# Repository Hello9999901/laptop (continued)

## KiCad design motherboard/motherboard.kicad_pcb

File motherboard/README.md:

# Motherboard

Too much to explain right now.

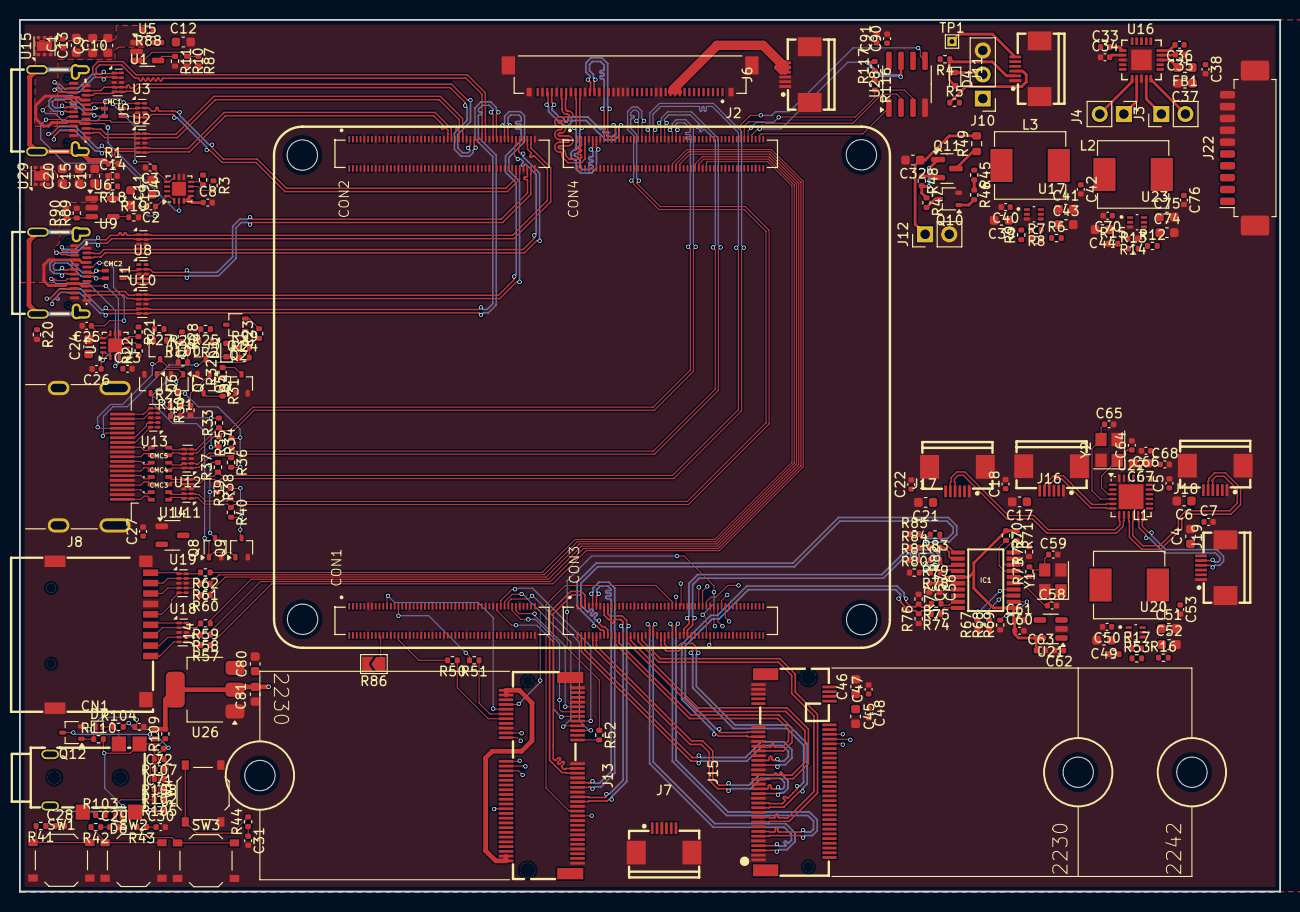
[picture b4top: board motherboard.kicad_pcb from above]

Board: 6 copper layers, 133.0 x 92.0 mm, 257 parts (0 on the bottom side), 253 nets.

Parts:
C1, C14: 100nF (+25V); C_0402_1005Metric
C2, C3, C25, C26: 220pF; C_0402_1005Metric
C4, C6, C11, C12, C13, C17, C19, C20, C21, C24, C32, C37, C67, C80, C81: 10uF; C_0603_1608Metric
C5, C7, C18, C22, C38, C48, C66, C71, C72, C90: 0.1uF; C_0402_1005Metric
C8, C23, C40, C42, C50, C53, C56, C61, C70, C76: 100nF; C_0402_1005Metric
C9, C10, C15, C16: 10uF (C913517); C_0603_1608Metric
C27, C33, C34, C35, C36, C47, C57, C60, C62, C63, C68, C73, C91: 1uF; C_0402_1005Metric
C28, C29, C30, C31: 1nF; C_0402_1005Metric
C39, C41, C43, C44, C45, C46, C49, C51, C52, C74, C75: 22uF; C_0603_1608Metric
C58, C59, C64, C65: 15pF; C_0402_1005Metric
CMC1, CMC2, CMC3, CMC4, CMC5, CMC6: ACM2012; FIL_ACM2012-900-2P-T001
CN1: PJ-332A-6A (3.5mm Jack); AUDIO-SMD_PJ-332A-6A
D3, D4: LRB521S-30T1G; D_SOD-523
D6, D7: LESD8D5.0CB1T5G; D_SOD-882
FB1: GZ1608D601TF; L_0603_1608Metric
IC1: PI6C557-05BLE; SOP65P640X120-20N
J1: USB_C_Receptacle; USB-C-SMD_TYPE-C-24P-QT
J2: 20455-040E-76 OLED IPEX; IPEX_20455-040E-76
J3: RIGHT SPEAKERS; PinHeader_1x02_P2.54mm_Vertical
J4: LEFT SPEAKERS; PinHeader_1x02_P2.54mm_Vertical
J5: Outer USB-C; USB-C-SMD_TYPE-C-24P-QT
J6: OLED EL POWER; FPC-SMD_6P-P0.50_XUNPU_FPC-05F-6PH20
J7: HALL SWITCH; FPC-SMD_6P-P0.50_XUNPU_FPC-05F-6PH20
J8: HDMI_A; HDMI_A_Molex_208658-1001_Horizontal
J10: DEBUG UART; PinHeader_1x03_P2.54mm_Vertical
J11: SYSTEM; FPC-SMD_6P-P0.50_XUNPU_FPC-05F-6PH20
J12: 5V FAN; PinHeader_1x02_P2.54mm_Vertical
J13: Bus_M.2_Socket_E; CONN-SMD_APCI0147-P001A
J14: Micro_SD_Card_Det1; TF-SMD_TF-CARD-H1.8
J15: Bus_M.2_Socket_M; CONN-SMD_AS0BC21-S30BM-7H
J16, J17, J18, J19: USB; FPC-SMD_6P-P0.50_XUNPU_FPC-05F-6PH20
J20: CM3588 Hirose Connector; CM3588
J22: BATTERY IN; Molex_PicoBlade_53261-1071_1x10-1MP_P1.25mm_Horizontal
L1, L3: MWSA0603S-3R3MT; L_Sunlord_MWSA0603S
L2: FXL0630-4R7-M; L_Sunlord_MWSA0603S
Q1, Q2, Q4, Q5, Q10, Q12: 2SK3018W; SOT-323_SC-70
Q3: L2N7002WT1G; SOT-323_SC-70
Q6, Q7, Q8, Q9: WNM6002-3/TR; SOT-323_SC-70
Q11: AO3415A; SOT-23
R1, R20: 1M; R_0402_1005Metric
R2, R3, R21, R22, R52, R111: 2.2k; R_0402_1005Metric
R4, R6, R7, R12, R16, R25, R27, R31, R32, R45, R54, R70, R71, R105, R106, R110, R116, R117: 10k; R_0402_1005Metric
R5, R57, R58, R59, R60, R61, R62, R74, R75, R78, R79, R82, R83, R107, R108: 33R; R_0402_1005Metric
R8, R17: 49.9k; R_0402_1005Metric
R9, R53: 510k; R_0402_1005Metric
R10, R87, R89, R90: 6.8k; R_0402_1005Metric
R11, R19, R109: 100k; R_0402_1005Metric
R13: 220k; R_0402_1005Metric
R14: 33k; R_0402_1005Metric
R15: 330k; R_0402_1005Metric
R18, R50, R51, R68, R69, R88, R102, R103, R104: 0R; R_0402_1005Metric
R23: 27k; R_0402_1005Metric
R24, R100, R101: 18k; R_0402_1005Metric
R26, R29, R99: 2k; R_0402_1005Metric
R28, R47: 1k; R_0402_1005Metric
R30: 47k; R_0402_1005Metric
R33, R34, R35, R36, R37, R38, R39, R40: 499R; R_0402_1005Metric
R41, R42, R43, R44, R46, R73: 100R; R_0402_1005Metric
R48, R72: 470R; R_0402_1005Metric
R49: 2.2R; R_0603_1608Metric
R67: 4.7k; R_0402_1005Metric
R76, R77, R80, R81, R84, R85: 49.9R; R_0402_1005Metric
R86: 0R; SolderJumper-2_P1.3mm_Open_TrianglePad1.0x1.5mm
SW1: PWR; SW_Push_1P1T_XKB_TS-1187A
SW2: RESET; SW_Push_1P1T_XKB_TS-1187A
SW3: MASK; SW_Push_1P1T_XKB_TS-1187A
SW4: RECOVERY; SW_Push_1P1T_XKB_TS-1187A
TP1: PWRON; TestPoint_THTPad_1.0x1.0mm_Drill0.5mm
U1, U2, U3, U8, U9, U10, U11, U12, U13, U18, U19: TPD4E02B04; USON-10_2.5x1.0mm_P0.5mm
U4, U7: FUSB302BMPX; WQFN-14-1EP_2.5x2.5mm_P0.5mm_EP1.45x1.45mm
U5, U6: SY6280AAC; SOT-23-5
U14: AP2331; SOT-23-3
U15, U29: TVS2200DRV; WSON-6-1EP_2x2mm_P0.65mm_EP1x1.6mm
U16: TPA2016D2RTJR; QFN50P400X400X80-21N
U17, U20, U23: TPS564257DRLR; SOT50P160X60-6N
U21: AP2127K-3.3; SOT-23-5
U22: CH334F; QFN-24-1EP_4x4mm_P0.5mm_EP2.6x2.6mm
U26: AMS1117-1.8; SOT-223-3_TabPin2
U28: SPI Flash; SOIC-8_3.9x4.9mm_P1.27mm
Y1: 25MHz; Crystal_SMD_3225-4Pin_3.2x2.5mm
Y2: 12MHz; Crystal_SMD_3225-4Pin_3.2x2.5mm

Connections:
+1V8: C81.1, R45.1, R109.2, R111.2, U26.2 (VO)
+3.3V: C8.1, C23.1, C41.1, C42.1, C43.1, C66.1, C67.1, C80.1, C90.1, C91.1, J2.17, J2.18, J2.19, J7.1, L3.2, Q2.1 (G), R2.1, R3.1, R4.2, R6.2, R21.1, R22.1, R23.1, R25.1, R27.1, R28.1, R31.1, R32.1, R116.1, R117.1, U4.3 (VDD), U4.4 (VDD), U7.3 (VDD), U7.4 (VDD), U21.3 (EN), U22.20 (VDD33), U26.3 (VI), U28.8 (VCC)
+3.3V_PCIE: C45.1, C46.1, C47.1, C48.1, C51.1, C52.1, C53.1, J13.2 (3.3V), J13.4 (3.3V), J13.72 (3.3V), J13.74 (3.3V), J15.2 (3.3V), J15.4 (3.3V), J15.12 (3.3V), J15.14 (3.3V), J15.16 (3.3V), J15.18 (3.3V), J15.70 (3.3V), J15.72 (3.3V), J15.74 (3.3V), L1.2, R16.2
+5V: C4.1, C5.1, C6.1, C7.1, C11.1, C12.1, C17.1, C18.1, C19.1, C21.1, C22.1, C24.1, C37.1, C38.1, C62.1, C68.1, C74.1, C75.1, C76.1, D3.2 (A), FB1.1, J16.6, J17.6, J18.6, J19.6, L2.2, Q1.1 (G), Q11.2 (S), R12.2, R18.1, R48.1, R88.1, U4.12 (VCONN), U4.13 (VCONN), U5.5 (IN), U6.5 (IN), U7.12 (VCONN), U7.13 (VCONN), U14.3 (IN), U16.4 (PVDDL_2), U16.5 (PVDDL), U16.11 (PVDDR_2), U16.12 (PVDDR), U21.1 (VIN), U22.19 (V5)
/Audio/L_AUDIO: C33.1, C72.1, J20.104, R104.2, R106.2
/Audio/L_DET: CN1.5, CN1.6, R109.1, R110.2
/Audio/L_HP: CN1.4, D7.2 (A2), R104.1
/Audio/MIC: CN1.1, R102.1
/Audio/R_AUDIO: C36.1, C71.1, J20.103, R103.2, R105.2
/Audio/R_HP: CN1.3, D6.2 (A2), R103.1
/BOOT_SARADC_IN0: C30.1, J20.15, R43.1
/GPIO0_A4/SDMMC_DET_L: J20.370, R62.1
/GPIO0_B2: J13.21 (~SDIO_WAKE), J20.247
/GPIO0_C4/UART0_RX_M0: J20.270, R52.1
/GPIO0_C5/UART0_TX_M0/PWM4_M0: J13.20 (~UART_WAKE), J20.272
/GPIO0_D3/CC_INT_L: J20.264, U4.5 (INT_N)
/GPIO0_D5: J20.268, U7.5 (INT_N)
/GPIO1_A0/UART6_RX_M1: J13.22 (UART_RXD), J20.273
/GPIO1_A1/UART6_TX_M1: J13.32 (UART_TXD), J20.275
/GPIO1_A2/I2C4_SDA_M3_TP: J13.36 (UART_RTS), J20.277
/GPIO1_A3/I2C4_SCL_M3_TP: J13.34 (UART_CTS), J20.279
/GPIO1_A4: J20.281, U28.6 (SCK)
/GPIO1_A7: J20.283, U16.18 (SDZ)
/GPIO1_C4/HP_DET_L: J20.108, Q12.3 (D), R111.1
/GPIO1_D2/TYPEC5V_PWREN_H: J20.239, R11.1, R19.1, U5.4 (ON), U6.4 (ON)
/GPIO1_D3/PWM1_M1: J20.241, R45.2, R46.1
/GPIO2_A6: J13.13 (SDIO_DATA0), J20.79
/GPIO2_A7: J13.15 (SDIO_DATA1), J20.81
/GPIO2_B0: J13.17 (SDIO_DATA2), J20.83
/GPIO2_B1: J13.19 (SDIO_DATA3), J20.85
/GPIO2_B2: J13.11 (SDIO_CMD), J20.87
/GPIO2_B3: J13.9 (SDIO_CLK), J20.89
/GPIO2_B7: J13.8 (PCM_CLK/I2S_SCK), J20.99
/GPIO2_C0: J13.10 (PCM_SYNC/I2S_WS), J20.21
/GPIO2_C3: J20.27, R51.2
/GPIO3_A0/SPI4_MISO_M1/PWM10_M0: J20.387, U28.5 (SI/IO0)
/GPIO3_A1/SPI4_MOSI_M1: J20.389, U28.2 (SO/IO1)
/GPIO3_A2/SPI4_CLK_M1/UART8_TX_M1: J20.391, R116.2, U28.3 (~WP/IO2)
/GPIO3_A3/SPI4_CS0_M1/UART8_RX_M1: J20.393, R117.2, U28.7 (~HOLD/IO3)
/GPIO3_A5: J20.397, U28.1 (~CS)
/GPIO3_A6/LCD_RST: J13.42 (VENDOR_DEFINED), J20.399
/GPIO4_A0/TP_2_INT_L: J13.53 (~CLKREQ0), J20.251
/GPIO4_A1/TP_2_RST_L: J13.55 (~PEWAKE0), J20.253
/GPIO4_A2: J13.52 (~PERST0), J20.255
/GPIO4_B4/PCIE30X4_CLKREQn_M1_L: J15.52 (~CLKREQ), J20.265
/GPIO4_B5/PCIE30X4_WAKEn_M1_L: J15.54 (~PEWAKE), J20.267
/GPIO4_B6/PCIE30X4_PERSTn_M1_L: J15.50 (~PERST), J20.269
/GPIO4_C2: J7.2, J20.26
/GPIO4_C3: J20.28, R50.2
/HDMI0_TX_ON_H: J20.369, Q6.1 (G), Q7.1 (G), Q8.1 (G), Q9.1 (G)
/HDMI1_TX0N: J2.29, J20.317
/HDMI1_TX0P: J2.28, J20.315
/HDMI1_TX1N: J2.32, J20.311
/HDMI1_TX1P: J2.31, J20.309
/HDMI1_TX2N: J2.35, J20.305
/HDMI1_TX2P: J2.34, J20.303
/HDMI1_TX3N: J2.38, J20.323
/HDMI1_TX3P: J2.37, J20.321
/HDMI1_TX_SBDN: J2.25, J20.329
/HDMI1_TX_SBDP: J2.26, J20.327
/HDMITX0_CEC_M0: J20.367, Q1.2 (S), R23.2
/HDMITX0_HPDIN_M0: J20.295, Q5.3 (D), R32.2
/HDMITX0_SCL_M0: J20.363, Q2.2 (S), R25.2
/HDMITX0_SDA_M0: J20.365, Q3.2 (S), R27.2
/HDMI_TX/CEC: J8.13 (CEC), Q1.3 (D), U13.1 (D1+), U13.10 (NC)
/HDMI_TX/HDMI0_5V: C27.1, J8.18 (+5V), U13.4 (D2+), U13.7 (NC), U14.2 (OUT)
/HDMI_TX/HDMI0_TX0N: CMC5.4, J20.347, R35.1, U12.2 (D1-), U12.9 (NC)
/HDMI_TX/HDMI0_TX0P: CMC5.3, J20.345, R36.1, U12.1 (D1+), U12.10 (NC)
/HDMI_TX/HDMI0_TX1N: CMC4.4, J20.341, R37.1, U11.5 (D2-), U11.6 (NC)
/HDMI_TX/HDMI0_TX1P: CMC4.3, J20.339, R38.1, U11.4 (D2+), U11.7 (NC)
/HDMI_TX/HDMI0_TX2N: CMC3.4, J20.335, R39.1, U11.2 (D1-), U11.9 (NC)
/HDMI_TX/HDMI0_TX2P: CMC3.3, J20.333, R40.1, U11.1 (D1+), U11.10 (NC)
/HDMI_TX/HDMI0_TX3N: CMC6.4, J20.353, R33.1, U12.5 (D2-), U12.6 (NC)
/HDMI_TX/HDMI0_TX3P: CMC6.3, J20.351, R34.1, U12.4 (D2+), U12.7 (NC)
/HDMI_TX/IN_TX0N: CMC5.1, J8.9 (D0-)
/HDMI_TX/IN_TX0P: CMC5.2, J8.7 (D0+)
/HDMI_TX/IN_TX1N: CMC4.1, J8.6 (D1-)
/HDMI_TX/IN_TX1P: CMC4.2, J8.4 (D1+)
/HDMI_TX/IN_TX2N: CMC3.1, J8.3 (D2-)
/HDMI_TX/IN_TX2P: CMC3.2, J8.1 (D2+)
/HDMI_TX/IN_TX3N: CMC6.1, J8.12 (CK-)
/HDMI_TX/IN_TX3P: CMC6.2, J8.10 (CK+)
/HDMI_TX/SBDN: J8.19 (HPD), J20.359, R29.1, R101.1, U13.5 (D2-), U13.6 (NC)
/HDMI_TX/SBDP: J8.14 (UTILITY), J20.357, U13.2 (D1-), U13.9 (NC)
/HDMI_TX/SCL: J8.15 (SCL), Q2.3 (D), R24.2, R99.2
/HDMI_TX/SDA: J8.16 (SDA), Q3.3 (D), R26.2, R100.2
/I2C6_SCL_M0: J20.296, R3.2, U4.6 (SCL), U16.19 (SDA)
/I2C6_SDA_M0: J20.298, R2.2, U4.7 (SDA), U16.17 (SCL)
/I2C7_SCL_M0: J20.107, R22.2, U7.6 (SCL)
/I2C7_SDA_M0: J20.105, R21.2, U7.7 (SDA)
/MIC_IN: J20.106, R102.2
/PCIE3.0-MKEY/+3.3V_PI6C: C56.1, C57.1, C60.1, C61.1, C63.1, IC1.1 (VDDXD), IC1.15 (VDDODA), R70.1, R71.1, U21.5 (VOUT)
/PCIE3.0-MKEY/CLK2N: IC1.13 (~CLK2), R79.1
/PCIE3.0-MKEY/CLK2P: IC1.14 (CLK2), R78.1
/PCIE3.0-MKEY/CLK3N: IC1.11 (~CLK3), R83.1
/PCIE3.0-MKEY/CLK3P: IC1.12 (CLK3), R82.1
/PCIE3.0-MKEY/PCIE30_REFCLK_A_N: J15.53 (REFCLKn), R75.2, R77.2
/PCIE3.0-MKEY/PCIE30_REFCLK_A_P: J15.55 (REFCLKp), R74.2, R76.2
/PCIE3.0-MKEY/X1: C58.1, IC1.5 (X1), Y1.1
/PCIE3.0-MKEY/X2: IC1.6 (X2), R73.1
/PCIE20_1_REFCLKN: J13.49 (REFCLKn0), J20.217
/PCIE20_1_REFCLKP: J13.47 (REFCLKp0), J20.215
/PCIE20_1_RXN: J13.41 (PERp0), J20.211
/PCIE20_1_RXP: J13.43 (PERn0), J20.209
/PCIE20_1_TXN: J13.37 (PETn0), J20.205
/PCIE20_1_TXP: J13.35 (PETp0), J20.203
/PCIE30_PORT0_REFCLKN: J20.218, R83.2, R85.2
/PCIE30_PORT0_REFCLKP: J20.216, R82.2, R84.2
/PCIE30_PORT0_RX0N: J15.41 (PERn0/SATA-B+), J20.206
/PCIE30_PORT0_RX0P: J15.43 (PERp0/SATA-B-), J20.204
/PCIE30_PORT0_RX1N: J15.29 (PERn1), J20.212
/PCIE30_PORT0_RX1P: J15.31 (PERp1), J20.210
/PCIE30_PORT0_TX0N: J15.47 (PETn0/SATA-A-), J20.224
/PCIE30_PORT0_TX0P: J15.49 (PETp0/SATA-A+), J20.222
/PCIE30_PORT0_TX1N: J15.35 (PETn1), J20.230
/PCIE30_PORT0_TX1P: J15.37 (PETp1), J20.228
/PCIE30_PORT1_REFCLKN: J20.260, R79.2, R81.2
/PCIE30_PORT1_REFCLKP: J20.258, R78.2, R80.2
/PCIE30_PORT1_RX2N: J15.17 (PERn2), J20.236
/PCIE30_PORT1_RX2P: J15.19 (PERp2), J20.234
/PCIE30_PORT1_RX3N: J15.5 (PERn3), J20.242
/PCIE30_PORT1_RX3P: J15.7 (PERp3), J20.240
/PCIE30_PORT1_TX2N: J15.23 (PETn2), J20.248
/PCIE30_PORT1_TX2P: J15.25 (PETp2), J20.246
/PCIE30_PORT1_TX3N: J15.11 (PETn3), J20.254
/PCIE30_PORT1_TX3P: J15.13 (PETp3), J20.252
/PMIC_EXT_EN_OUT: J20.19, U17.5 (EN), U20.5 (EN), U23.5 (EN)
/PWRON_L: C28.1, J20.17, R41.1
/RECOVERY: C31.1, J20.101, R44.1
/RESET_L: C29.1, J20.16, R42.1
/SD Card/CLK: J14.5 (CLK), J20.360, U19.5 (D2-), U19.6 (NC)
/SD Card/CMD: J14.3 (CMD), R59.2, U18.2 (D1-), U18.9 (NC)
/SD Card/D0: J14.7 (DAT0), R60.2, U19.4 (D2+), U19.7 (NC)
/SD Card/D1: J14.8 (DAT1), R61.2, U19.2 (D1-), U19.9 (NC)
/SD Card/D2: J14.1 (DAT2), R57.2, U18.5 (D2-), U18.6 (NC)
/SD Card/D3: J14.2 (DAT3/CD), R58.2, U18.4 (D2+), U18.7 (NC)
/SD Card/DET: J14.9 (DET), R62.2, U19.1 (D1+), U19.10 (NC)
/SD Card/VDD: J14.4 (VDD), J20.358, U18.1 (D1+), U18.10 (NC)
/SDMMC0_CMD: J20.356, R59.1
/SDMMC0_D0: J20.364, R60.1
/SDMMC0_D1: J20.366, R61.1
/SDMMC0_D2: J20.352, R57.1
/SDMMC0_D3: J20.354, R58.1
/System/BOOT_SARADC: J11.4, R43.2, SW3.1 (A)
/System/PWRON_L_IN: J11.6, R41.2, SW1.1 (A), TP1.1
/System/RECOVERY_IN: R44.2, SW4.1 (A)
/System/RESET_L_IN: J11.5, R42.2, SW2.1 (A)
/System/UART_RX: D4.2 (A), J11.2, J20.22, R4.1
/System/UART_TX: J11.3, J20.20, R5.1
/USB2.0/D1_N: J19.5, U22.11 (DM1)
/USB2.0/D1_P: J19.4, U22.12 (DP1)
/USB2.0/D2_N: J18.5, U22.9 (DM2)
/USB2.0/D2_P: J18.4, U22.10 (DP2)
/USB2.0/D3_N: J17.5, U22.7 (DM3)
/USB2.0/D3_P: J17.4, U22.8 (DP3)
/USB2.0/D4_N: J16.5, U22.5 (DM4)
/USB2.0/D4_P: J16.4, U22.6 (DP4)
/USB2.0/X1: C64.1, U22.3 (XO), Y2.1
/USB2.0/X2: C65.1, U22.4 (XI), Y2.3
/USB20_HOST0_DN: J20.324, U22.14 (DMU)
/USB20_HOST0_DP: J20.322, U22.15 (DPU)
/USB20_HOST1_DN: J13.5 (USB_D-), J20.318
/USB20_HOST1_DP: J13.3 (USB_D+), J20.316
/USBC0/CC1: C3.1, J5.A5 (CC1), U4.10 (CC1), U4.11 (CC1)
/USBC0/CC2: C2.1, J5.B5 (CC2), U4.1 (CC2), U4.14 (CC2)
/USBC0/D+: CMC1.4, J20.190, U3.2 (D1-), U3.9 (NC)
/USBC0/D-: CMC1.3, J20.192, U3.4 (D2+), U3.7 (NC)
/USBC0/IN_D+: CMC1.1, J5.A6 (D+), J5.B6 (D+)
/USBC0/IN_D-: CMC1.2, J5.A7 (D-), J5.B7 (D-)
/USBC0/RX1+: J5.B11 (RX1+), J20.171, U1.1 (D1+), U1.10 (NC)
/USBC0/RX1-: J5.B10 (RX1-), J20.173, U1.2 (D1-), U1.9 (NC)
/USBC0/RX2+: J5.A11 (RX2+), J20.159, U2.2 (D1-), U2.9 (NC)
/USBC0/RX2-: J5.A10 (RX2-), J20.161, U2.1 (D1+), U2.10 (NC)
/USBC0/SBUS1: J5.A8 (SBU1), J20.304, U3.5 (D2-), U3.6 (NC)
/USBC0/SBUS2: J5.B8 (SBU2), J20.306, U3.1 (D1+), U3.10 (NC)
/USBC0/TX1+: J5.A2 (TX1+), J20.165, U1.4 (D2+), U1.7 (NC)
/USBC0/TX1-: J5.A3 (TX1-), J20.167, U1.5 (D2-), U1.6 (NC)
/USBC0/TX2+: J5.B2 (TX2+), J20.153, U2.5 (D2-), U2.6 (NC)
/USBC0/TX2-: J5.B3 (TX2-), J20.155, U2.4 (D2+), U2.7 (NC)
/USBC0/VBUS: C1.1, C9.1, C10.1, C13.1, J5.A4 (VBUS), J5.A9 (VBUS), J5.B4 (VBUS), J5.B9 (VBUS), R88.2, U4.2 (VBUS), U5.1 (OUT), U15.1 (GND), U15.2 (GND), U15.3 (GND), U15.7 (GND)
/USBC1/CC1: C25.1, J1.A5 (CC1), U7.10 (CC1), U7.11 (CC1)
/USBC1/CC2: C26.1, J1.B5 (CC2), U7.1 (CC2), U7.14 (CC2)
/USBC1/D+: CMC2.4, J20.196, U8.2 (D1-), U8.9 (NC)
/USBC1/D-: CMC2.3, J20.198, U8.4 (D2+), U8.7 (NC)
/USBC1/IN_D+: CMC2.1, J1.A6 (D+), J1.B6 (D+)
/USBC1/IN_D-: CMC2.2, J1.A7 (D-), J1.B7 (D-)
/USBC1/RX1+: J1.B11 (RX1+), J20.195, U9.1 (D1+), U9.10 (NC)
/USBC1/RX1-: J1.B10 (RX1-), J20.197, U9.2 (D1-), U9.9 (NC)
/USBC1/RX2+: J1.A11 (RX2+), J20.183, U10.2 (D1-), U10.9 (NC)
/USBC1/RX2-: J1.A10 (RX2-), J20.185, U10.1 (D1+), U10.10 (NC)
/USBC1/SBUS1: J1.A8 (SBU1), J20.310, U8.5 (D2-), U8.6 (NC)
/USBC1/SBUS2: J1.B8 (SBU2), J20.312, U8.1 (D1+), U8.10 (NC)
/USBC1/TX1+: J1.A2 (TX1+), J20.189, U9.4 (D2+), U9.7 (NC)
/USBC1/TX1-: J1.A3 (TX1-), J20.191, U9.5 (D2-), U9.6 (NC)
/USBC1/TX2+: J1.B2 (TX2+), J20.177, U10.5 (D2-), U10.6 (NC)
/USBC1/TX2-: J1.B3 (TX2-), J20.179, U10.4 (D2+), U10.7 (NC)
/USBC1/VBUS: C14.1, C15.1, C16.1, C20.1, J1.A4 (VBUS), J1.A9 (VBUS), J1.B4 (VBUS), J1.B9 (VBUS), R18.2, U6.1 (OUT), U7.2 (VBUS), U29.1 (GND), U29.2 (GND), U29.3 (GND), U29.7 (GND)
/VDC_MODE: J20.18, R86.1
GND: C1.2, C2.2, C3.2, C4.2, C5.2, C6.2, C7.2, C8.2, C9.2, C10.2, C11.2, C12.2, C13.2, C14.2, C15.2, C16.2, C17.2, C18.2, C19.2, C20.2, C21.2, C22.2, C23.2, C24.2, C25.2, C26.2, C27.2, C28.2, C29.2, C30.2, C31.2, C32.2, C34.1, C35.1, C37.2, C38.2, C39.2, C40.2, C41.2, C42.2, C43.2, C44.2, C45.2, C46.2, C47.2, C48.2, C49.2, C50.2, C51.2, C52.2, C53.2, C56.2, C57.2, C58.2, C59.2, C60.2, C61.2, C62.2, C63.2, C64.2, C65.2, C66.2, C67.2, C68.2, C70.2, C73.2, C74.2, C75.2, C76.2, C80.2, C81.2, C90.2, C91.2, D6.1 (A1), D7.1 (A1), IC1.9 (GNDXD), IC1.16 (GNDODA), J1.A1 (GND), J1.A12 (GND), J1.B1 (GND), J1.B12 (GND), J2.14, J2.15, J2.21, J2.22, J2.23, J2.24, J2.27, J2.30, J2.33, J2.36, J2.39, J2.S1 (SHIELD), J2.S2 (SHIELD), J2.S3 (SHIELD), J2.S4 (SHIELD), J5.A1 (GND), J5.A12 (GND), J5.B1 (GND), J5.B12 (GND), J6.1, J6.2, J6.3, J6.MP (MountPin), J7.3, J7.MP (MountPin), J8.2 (D2S), J8.5 (D1S), J8.8 (D0S), J8.11 (CKS), J8.17 (GND), J8.SH, J10.3, J11.1, J11.MP (MountPin), J12.2, J13.1 (GND), J13.7 (GND), J13.18 (GND), J13.33 (GND), J13.39 (GND), J13.45 (GND), J13.51 (GND), J13.57 (GND), J13.63 (GND), J13.69 (GND), J13.75 (GND), J14.6 (VSS), J14.10 (SHIELD), J15.1 (GND), J15.3 (GND), J15.9 (GND), J15.15 (GND), J15.21 (GND), J15.27 (GND), J15.33 (GND), J15.39 (GND), J15.45 (GND), J15.51 (GND), J15.57 (GND), J15.71 (GND), J15.73 (GND), J15.75 (GND), J16.1, J16.MP (MountPin), J17.1, J17.MP (MountPin), J18.1, J18.MP (MountPin), J19.1, J19.MP (MountPin), J20.11, J20.12, J20.13, J20.24, J20.33, J20.34, J20.39, J20.40, J20.45, J20.46, J20.51, J20.52, J20.57, J20.58, J20.63, J20.64, J20.69, J20.70, J20.73, J20.76, J20.77, J20.82, J20.88, J20.91, J20.94, J20.100, J20.109, J20.110, J20.115, J20.116, J20.121, J20.122, J20.127, J20.128, J20.133, J20.134, J20.139, J20.140, J20.145, J20.146, J20.151, J20.152, J20.157, J20.158, J20.163, J20.164, J20.169, J20.170, J20.175, J20.176, J20.181, J20.182, J20.187, J20.188, J20.193, J20.194, J20.199, J20.200, J20.201, J20.202, J20.207, J20.208, J20.213, J20.214, J20.219, J20.220, J20.225, J20.226, J20.231, J20.232, J20.237, J20.238, J20.244, J20.249, J20.250, J20.256, J20.259, J20.262, J20.271, J20.284, J20.285, J20.294, J20.301, J20.302, J20.307, J20.308, J20.313, J20.314, J20.319, J20.320, J20.325, J20.326, J20.331, J20.332, J20.337, J20.338, J20.343, J20.344, J20.349, J20.350, J20.355, J20.361, J20.362, J20.368, J20.380, J20.383, J20.396, J22.6, J22.7, J22.8, J22.9, J22.10, J22.MP (MountPin), Q4.2 (S), Q5.2 (S), Q6.2 (S), Q7.2 (S), Q8.2 (S), Q9.2 (S), Q10.2 (S), Q12.2 (S), R1.2, R7.1, R10.2, R11.2, R14.1, R15.1, R19.2, R20.2, R30.1, R54.1, R67.1, R68.1, R69.1, R72.1, R76.1, R77.1, R80.1, R81.1, R84.1, R85.1, R86.2, R87.2, R89.2, R90.2, SW1.2 (B), SW2.2 (B), SW3.2 (B), SW4.2 (B), U1.3 (GND), U1.8 (GND), U2.3 (GND), U2.8 (GND), U3.3 (GND), U3.8 (GND), U4.8 (GND), U4.9 (GND), U4.15 (GND), U5.2 (GND), U6.2 (GND), U7.8 (GND), U7.9 (GND), U7.15 (GND), U8.3 (GND), U8.8 (GND), U9.3 (GND), U9.8 (GND), U10.3 (GND), U10.8 (GND), U11.3 (GND), U11.8 (GND), U12.3 (GND), U12.8 (GND), U13.3 (GND), U13.8 (GND), U14.1 (GND), U15.4 (IN), U15.5 (IN), U15.6 (IN), U16.3 (AGND), U16.8 (PGND), U16.21 (EP), U17.3 (GND), U18.3 (GND), U18.8 (GND), U19.3 (GND), U19.8 (GND), U20.3 (GND), U21.2 (GND), U22.24 (PWREN#), U22.25 (GND), U23.3 (GND), U26.1 (GND), U28.4 (GND), U29.4 (IN), U29.5 (IN), U29.6 (IN), Y1.2, Y1.4, Y2.2, Y2.4
GND_AUDUO: CN1.2, J20.102, R105.1, R106.1, R107.1, R108.1
unnamed: C59.1, R73.2, Y1.3
unnamed: C71.2, R108.2
unnamed: C72.2, R107.2
unnamed: D4.1 (K), J10.2
unnamed: IC1.20 (CLK0), R74.1
unnamed: IC1.10 (IREF), R72.2
unnamed: IC1.8 (OE), R71.2
unnamed: IC1.2 (S0), R69.2
unnamed: IC1.3 (S1), R68.2
unnamed: IC1.4 (S2), R67.2
unnamed: IC1.19 (~CLK0), R75.1
unnamed: IC1.7 (~PD), R70.2
unnamed: J1.S1 (SHIELD), R20.1
unnamed: J3.1, U16.9 (OUTR-)
unnamed: J3.2, U16.10 (OUTR+)
unnamed: J4.1, U16.7 (OUTL-)
unnamed: J4.2, U16.6 (OUTL+)
unnamed: J2.10, J2.11, J2.12, J6.4, J6.5, J6.6
unnamed: J10.1, R5.2
unnamed: C32.1, J12.1, R49.2
unnamed: Q3.1 (G), R28.2
unnamed: Q4.3 (D), Q5.1 (G), R31.2
unnamed: Q4.1 (G), R29.2, R30.2, R101.2
unnamed: Q6.3 (D), R33.2, R34.2
unnamed: Q7.3 (D), R35.2, R36.2
unnamed: Q8.3 (D), R37.2, R38.2
unnamed: Q9.3 (D), R39.2, R40.2
unnamed: Q10.3 (D), R47.2
unnamed: Q10.1 (G), R46.2
unnamed: Q11.3 (D), R49.1
unnamed: Q11.1 (G), R47.1, R48.2
unnamed: C73.1, Q12.1 (G), R110.1
unnamed: R7.2, R8.1, R9.1
unnamed: R10.1, R87.1, U5.3 (ISET)
unnamed: R13.1, R14.2, R15.2
unnamed: R17.1, R53.1, R54.2
unnamed: D3.1 (K), R24.1, R26.1, R99.1, R100.1
unnamed: R89.1, R90.1, U6.3 (ISET)
unnamed: FB1.2, U16.13 (AVDD)
unnamed: C33.2, U16.1 (INL+)
unnamed: C34.2, U16.2 (INL-)
unnamed: C36.2, U16.15 (INR+)
unnamed: C35.2, U16.14 (INR-)
unnamed: R8.2, R9.2, U17.6 (FB)
unnamed: R6.1, U17.4 (PG)
unnamed: L3.1, U17.2 (SW)
unnamed: R17.2, R53.2, U20.6 (FB)
unnamed: R16.1, U20.4 (PG)
unnamed: L1.1, U20.2 (SW)
unnamed: R13.2, U23.6 (FB)
unnamed: R12.1, U23.4 (PG)
unnamed: L2.1, U23.2 (SW)
VDD: C39.1, C40.1, C44.1, C49.1, C50.1, C70.1, J20.1, J20.2, J20.3, J20.4, J20.5, J20.6, J20.7, J20.8, J20.9, J20.10, J22.1, J22.2, J22.3, J22.4, J22.5, U17.1 (VIN), U20.1 (VIN), U23.1 (VIN)

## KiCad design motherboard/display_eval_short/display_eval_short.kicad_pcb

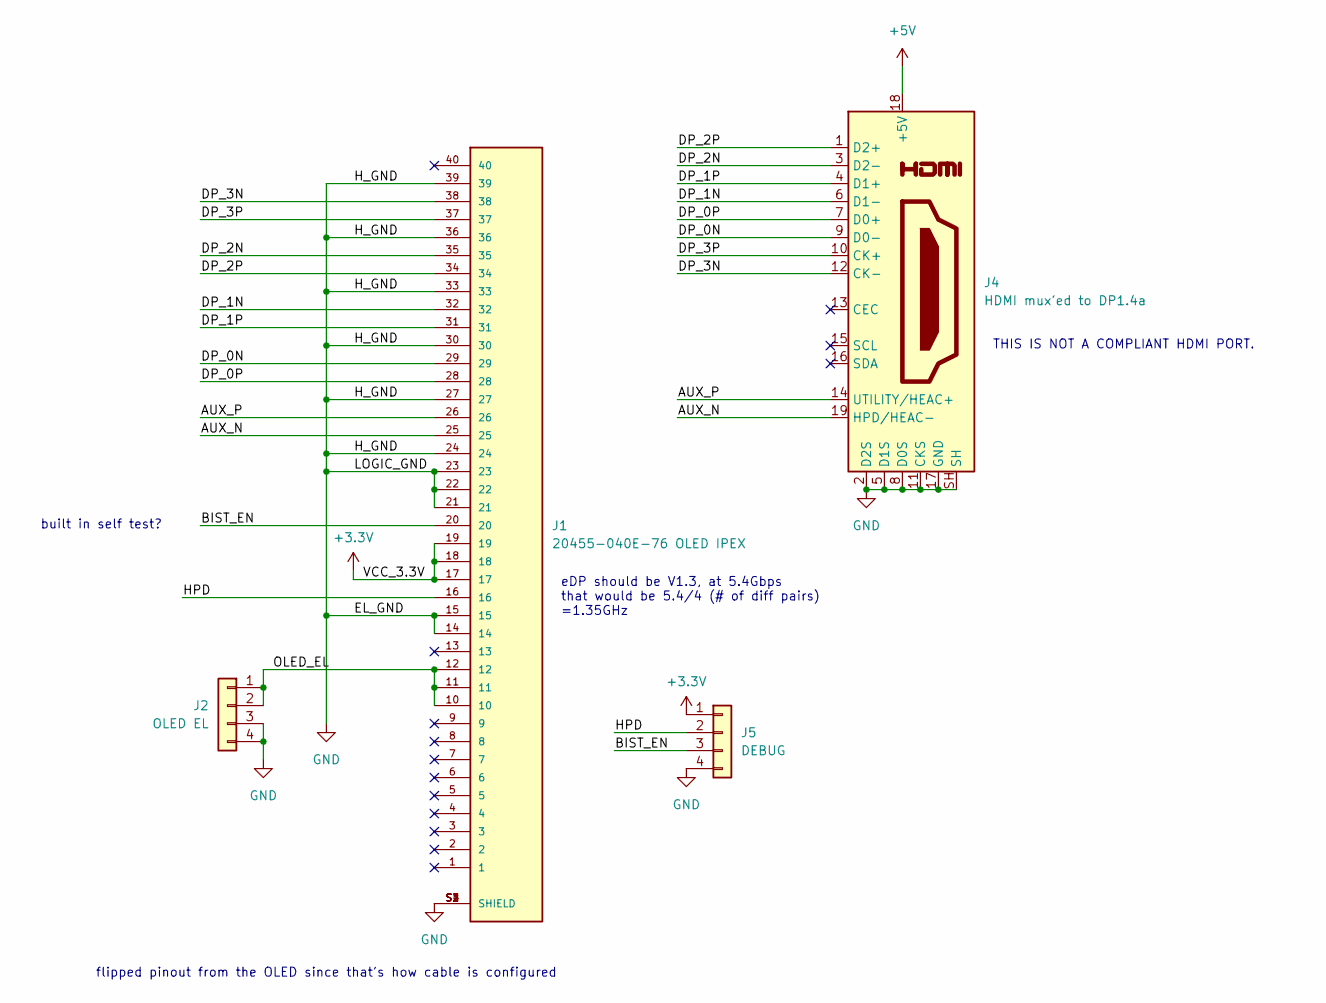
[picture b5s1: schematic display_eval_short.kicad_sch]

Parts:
J1: 20455-040E-76 OLED IPEX; IPEX_20455-040E-76; LCSC C7527731
J2: OLED EL; PinHeader_1x04_P2.54mm_Vertical
J4: HDMI mux'ed to DP1.4a; HDMI-SMD_HYC109-HDMIA19-160; LCSC C720616
J5: DEBUG; PinHeader_1x04_P2.54mm_Vertical

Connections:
+3.3V: J1.17, J1.18, J1.19, J5.1
+5V: J4.18 (+5V)
/AUX_N: J1.25, J4.19 (HPD/HEAC-)
/AUX_P: J1.26, J4.14 (UTILITY/HEAC+)
/BIST_EN: J1.20, J5.3
/DP_0N: J1.29, J4.9 (D0-)
/DP_0P: J1.28, J4.7 (D0+)
/DP_1N: J1.32, J4.6 (D1-)
/DP_1P: J1.31, J4.4 (D1+)
/DP_2N: J1.35, J4.3 (D2-)
/DP_2P: J1.34, J4.1 (D2+)
/DP_3N: J1.38, J4.12 (CK-)
/DP_3P: J1.37, J4.10 (CK+)
/HPD: J1.16, J5.2
/OLED_EL: J1.10, J1.11, J1.12, J2.1, J2.2
GND: J1.14, J1.15, J1.21, J1.22, J1.23, J1.24, J1.27, J1.30, J1.33, J1.36, J1.39, J1.S1 (SHIELD), J1.S2 (SHIELD), J1.S3 (SHIELD), J1.S4 (SHIELD), J2.3, J2.4, J4.2 (D2S), J4.5 (D1S), J4.8 (D0S), J4.11 (CKS), J4.17 (GND), J4.SH, J5.4

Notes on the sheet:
THIS IS NOT A COMPLIANT HDMI PORT.
eDP should be V1.3, at 5.4Gbps that would be 5.4/4 (# of diff pairs) =1.35GHz
flipped pinout from the OLED since that's how cable is configured
built in self test?

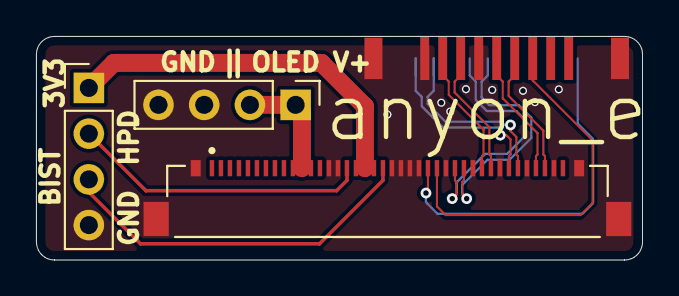
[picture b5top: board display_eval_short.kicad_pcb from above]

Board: 4 copper layers, 33.7 x 12.4 mm, 4 parts (1 on the bottom side), 15 nets.

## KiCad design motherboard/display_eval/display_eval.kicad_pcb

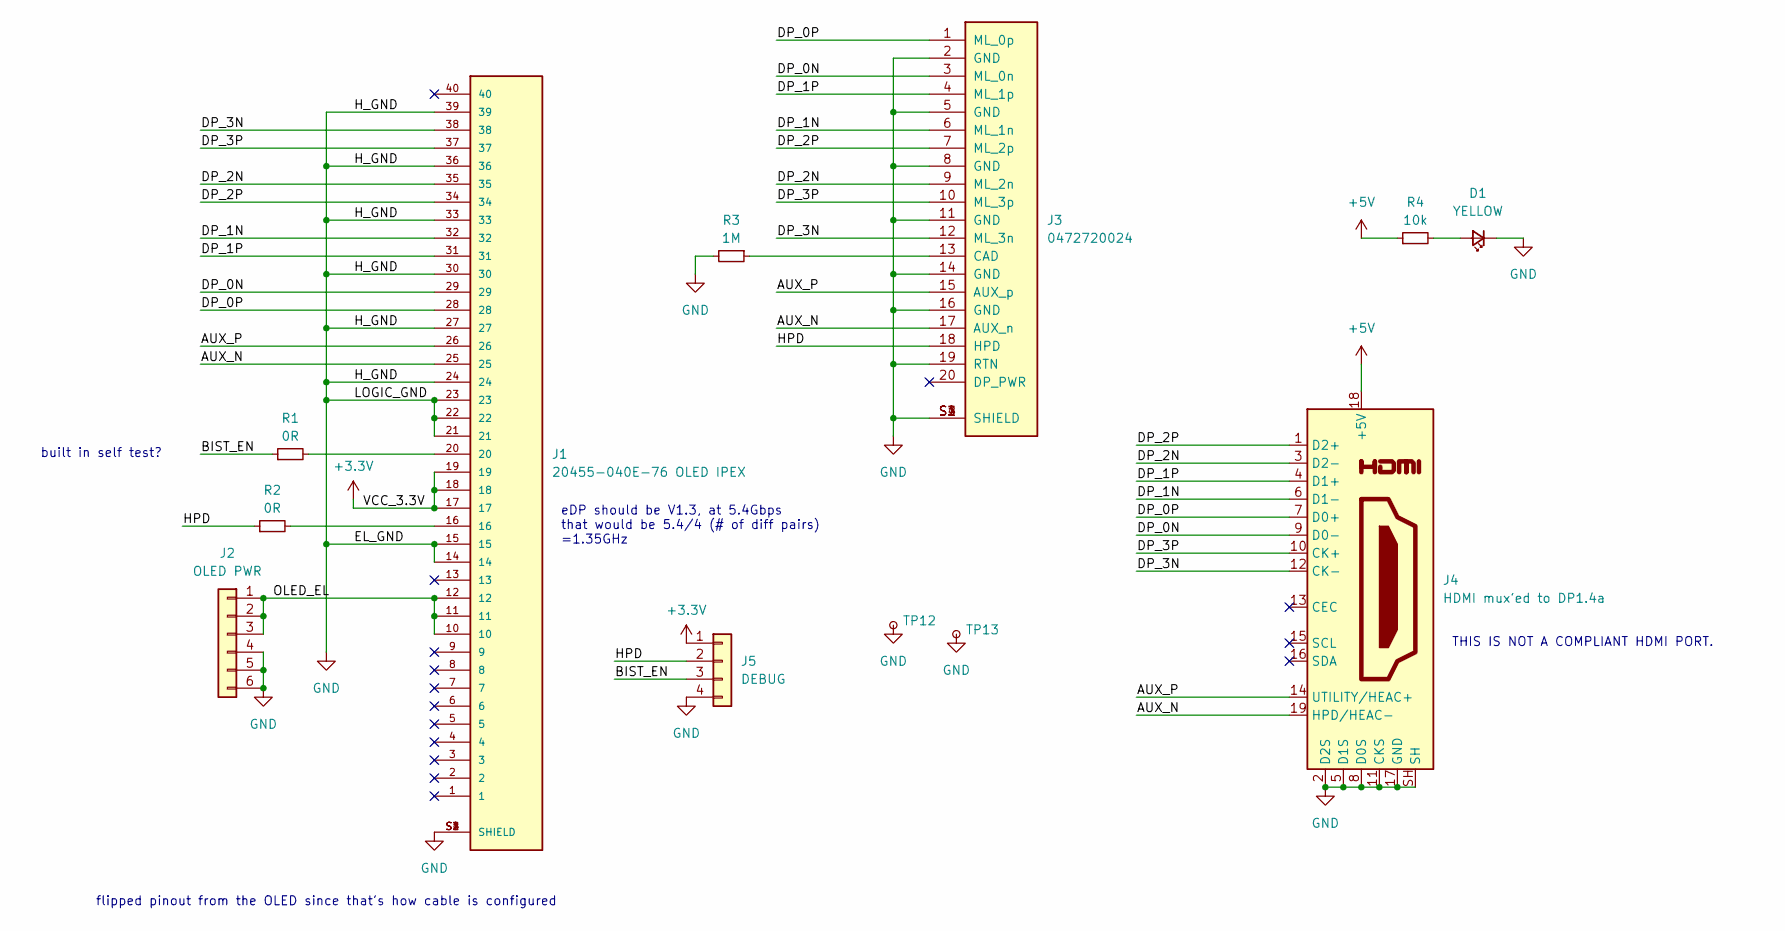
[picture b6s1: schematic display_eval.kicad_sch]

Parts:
D1: YELLOW; LED_0603_1608Metric; LCSC C2296
J1: 20455-040E-76 OLED IPEX; IPEX_20455-040E-76; LCSC C7527731
J2: OLED PWR; PinHeader_1x06_P2.54mm_Vertical
J3: 0472720024; MOLEX_0472720024; PARTREV D; LCSC C711350
J4: HDMI mux'ed to DP1.4a; HDMI_A_Molex_208658-1001_Horizontal; LCSC C720616
J5: DEBUG; PinHeader_1x04_P2.54mm_Vertical
R1: 0R; R_0603_1608Metric
R2: 0R; R_0603_1608Metric; LCSC C21189
R3: 1M; R_0603_1608Metric; LCSC C22935
R4: 10k; R_0603_1608Metric; LCSC C25804
TP12, TP13: TestPoint_THTPad_D2.0mm_Drill1.0mm

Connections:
+3.3V: J1.17, J1.18, J1.19, J5.1
+5V: J4.18 (+5V), R4.1
/AUX_N: J1.25, J3.17 (AUX_n), J4.19 (HPD/HEAC-)
/AUX_P: J1.26, J3.15 (AUX_p), J4.14 (UTILITY/HEAC+)
/BIST_EN: J5.3, R1.1
/DP_0N: J1.29, J3.3 (ML_0n), J4.9 (D0-)
/DP_0P: J1.28, J3.1 (ML_0p), J4.7 (D0+)
/DP_1N: J1.32, J3.6 (ML_1n), J4.6 (D1-)
/DP_1P: J1.31, J3.4 (ML_1p), J4.4 (D1+)
/DP_2N: J1.35, J3.9 (ML_2n), J4.3 (D2-)
/DP_2P: J1.34, J3.7 (ML_2p), J4.1 (D2+)
/DP_3N: J1.38, J3.12 (ML_3n), J4.12 (CK-)
/DP_3P: J1.37, J3.10 (ML_3p), J4.10 (CK+)
/HPD: J3.18 (HPD), J5.2, R2.1
/OLED_EL: J1.10, J1.11, J1.12, J2.1, J2.2, J2.3
GND: D1.1 (K), J1.14, J1.15, J1.21, J1.22, J1.23, J1.24, J1.27, J1.30, J1.33, J1.36, J1.39, J1.S1 (SHIELD), J1.S2 (SHIELD), J1.S3 (SHIELD), J1.S4 (SHIELD), J2.4, J2.5, J2.6, J3.2 (GND), J3.5 (GND), J3.8 (GND), J3.11 (GND), J3.14 (GND), J3.16 (GND), J3.19 (RTN), J3.S1 (SHIELD), J3.S2 (SHIELD), J3.S3 (SHIELD), J3.S4 (SHIELD), J4.2 (D2S), J4.5 (D1S), J4.8 (D0S), J4.11 (CKS), J4.17 (GND), J4.SH, J5.4, R3.2, TP12.1, TP13.1
unnamed: D1.2 (A), R4.2
unnamed: J1.16, R2.2
unnamed: J1.20, R1.2
unnamed: J3.13 (CAD), R3.1

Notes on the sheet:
THIS IS NOT A COMPLIANT HDMI PORT.
eDP should be V1.3, at 5.4Gbps that would be 5.4/4 (# of diff pairs) =1.35GHz
flipped pinout from the OLED since that's how cable is configured
built in self test?

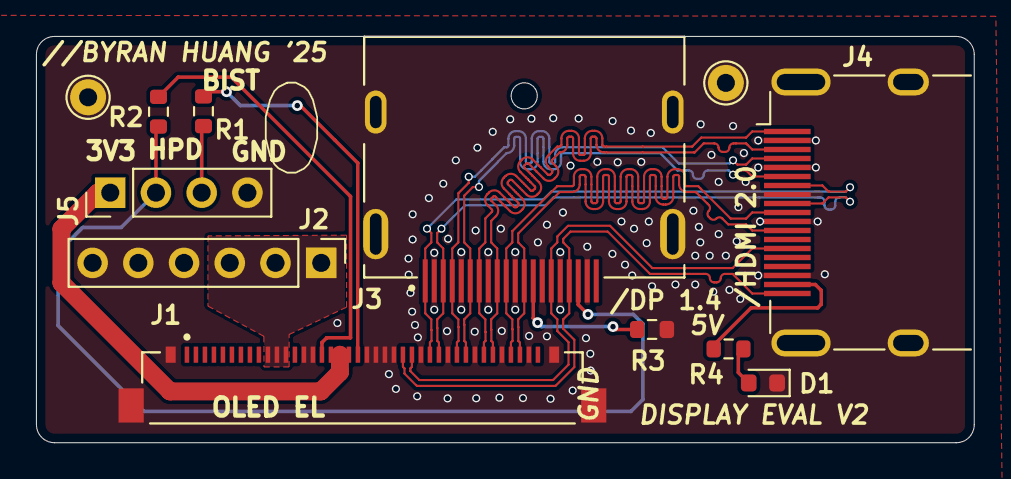
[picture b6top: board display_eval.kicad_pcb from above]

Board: 4 copper layers, 52.1 x 22.6 mm, 12 parts (0 on the bottom side), 20 nets.

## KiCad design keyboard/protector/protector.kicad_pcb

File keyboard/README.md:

# Keyboard

nRF52840-based wireless mechanical keyboard with Cherry ULP switches.

Keycap model: [https://cad.onshape.com/documents/84a4de0481dc58ca7a1fb22c/w/5ff1a0cc24fa744c0cb7a3a5/e/e79186c43fe11bbd17587153](https://cad.onshape.com/documents/84a4de0481dc58ca7a1fb22c/w/5ff1a0cc24fa744c0cb7a3a5/e/e79186c43fe11bbd17587153)

The full keyboard CAD is in the main `chassis` OnShape link.

Other sized keycaps modified from Carin keyboard with Blender (very sketchy and not very reproducible, so I won't put it up)

CAD model modified and credits: [here](https://www.reddit.com/r/ErgoMechKeyboards/comments/zpo9h6/mask200_4x6_split_keyboard_with_cherry_mxulp_keys/)

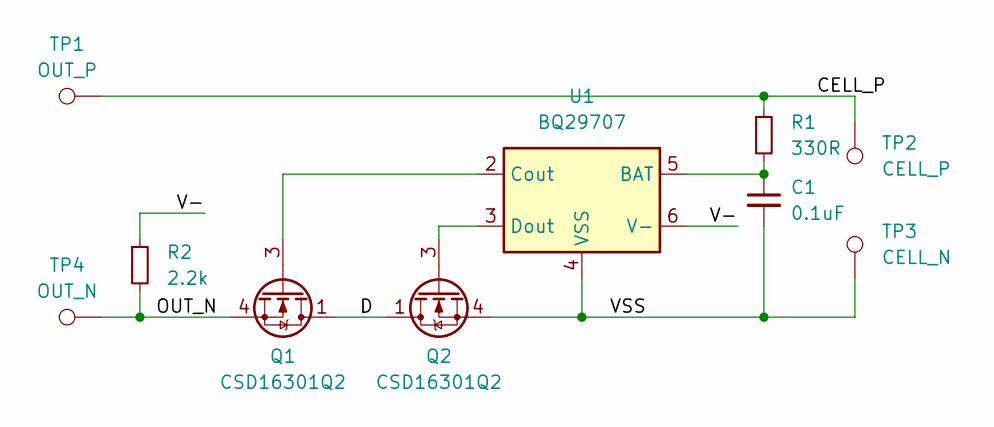
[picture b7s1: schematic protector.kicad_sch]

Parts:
C1: 0.1uF; C_0402_1005Metric; LCSC C307331
Q1, Q2: CSD16301Q2; Texas_DQK; LCSC C140340
R1: 330R; R_0402_1005Metric; LCSC C25104
R2: 2.2k; R_0402_1005Metric; LCSC C25879
TP1: OUT_P; TestPoint_Pad_4.0x4.0mm
TP2: CELL_P; TestPoint_Pad_4.0x4.0mm
TP3: CELL_N; TestPoint_Pad_4.0x4.0mm
TP4: OUT_N; TestPoint_Pad_4.0x4.0mm
U1: BQ29707; WSON-6_1.5x1.5mm_P0.5mm; LCSC C2864878

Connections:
/CELL_P: R1.1, TP1.1, TP2.1
/D: Q1.1 (D), Q1.2 (D), Q1.5 (D), Q1.6 (D), Q1.8 (D), Q2.1 (D), Q2.2 (D), Q2.5 (D), Q2.6 (D), Q2.8 (D)
/OUT_N: Q1.4 (S), Q1.7 (S), R2.2, TP4.1
/V-: R2.1, U1.6 (V-)
/VSS: C1.2, Q2.4 (S), Q2.7 (S), TP3.1, U1.4 (VSS)
unnamed: Q1.3 (G), U1.2 (Cout)
unnamed: Q2.3 (G), U1.3 (Dout)
unnamed: C1.1, R1.2, U1.5 (BAT)

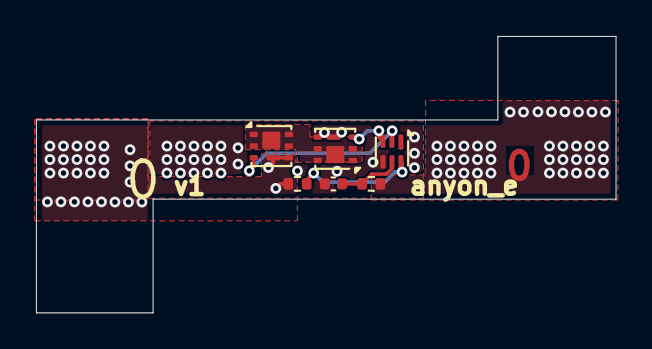
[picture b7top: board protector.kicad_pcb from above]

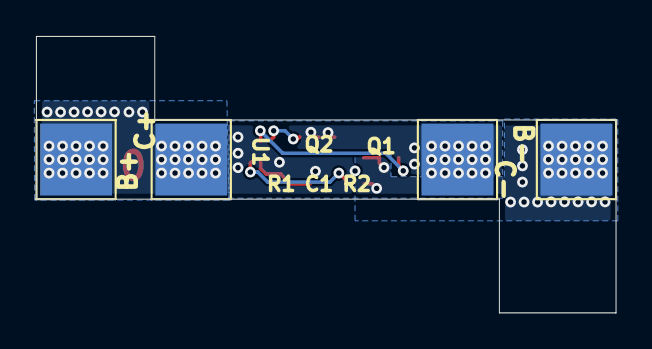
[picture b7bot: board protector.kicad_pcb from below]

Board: 2 copper layers, 32.2 x 15.4 mm, 10 parts (4 on the bottom side), 8 nets.
